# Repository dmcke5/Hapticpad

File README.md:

# CNCDan - Haptic Pad

A 6 button macropad with a display for button labels and a mouse knob with haptic feedback!

[Project Video Link](https://youtu.be/bNUKRJQjuvQ)

#### Features

- 6 Programmable  Macro Buttons
- 128x64 OLED display for button labels and Icons
- Support for up to 256 profiles for a total of 1536 Macros!
- Easy XML configuration, no special drivers required!
- Macro button combinations can be configured with up to 3 simultaneous buttons or 3 seperate button presses with configurable delays between them.
- Micro SD Storage for button labels and config files.
- Haptic feedback mouse wheel with three different modes. Clicky, Twist and Momentum
- RGB ring with configurable colours and 5 different display modes. Halo, Bands, Breath, Rainbow, Solid and Off.
- Easy profile switching with up down profile buttons or profile list display.
- The Last profile is stored to the SD card so the macro pad will start on whichever profile was last active.

#### Bill of Materials

1x 128x64 OLED Display - https://www.waveshare.com/2.42inch-oled-module.htm

1x Magnetic Encoder Board - https://www.aliexpress.com/item/1005007469177411.html

1x 2804 100kv Brushless Gimbal Motor - https://www.aliexpress.com/item/1005006008489660.html

6x Kailh Low Profile Switches - https://www.aliexpress.com/item/1005005066585322.html

1x RP2040-Plus Board - https://www.waveshare.com/rp2040-plus.htm

1x TMC6300 Motor Driver Board - https://www.sparkfun.com/sparkfun-brushless-motor-driver-3-phase-tmc6300.html

1x Micro SD Module - https://www.aliexpress.com/item/1005010587984346.html

4x 6x1mm Magnets - https://www.aliexpress.com/item/1005009894772141.html

2x Tactile Buttons - https://www.digikey.com/en/products/detail/panasonic-electronic-components/EVQ-Q2B03W/762882 (These are the ones I used, but shipping is expensive)

2x Alternative Tactile Buttons - https://www.aliexpress.com/item/1005008326208629.html (These seem like a suitable replacement for the EVQ-Q2B03W switches but I haven't tried them)

The following parts are optional if you want to include the LEDS:

20x WS2811 LED's - https://www.aliexpress.com/item/32776731877.html

20x 0.1uF (100nF) 0603 Capacitors - https://www.aliexpress.com/item/32966526545.html

#### Hardware

9x M3x5x5 Threaded Inserts (only needed for printed housing)

3x M3x6 SHCS

2x M3x10 SHCS

10x M2.5x4 SHCS

4x M3x6 CSK

### Printing Instructions

#### - Printed version
Print all files in the 3D Files/STL's folder. You will need 6 of the keycap file, two of the Menu button file and two of the PCB spacer file.

#### - Machined Version
Print all files in the 3D Files/STL's folder except: "Custom Keycap.STL", "Macro Pad - Printed Version.STL" and "Menu Button Printed.STL"
Get all of the .STEP files in the 3D Files/STEP folder machined. Don't include the Macropad Assembly .STEP file from the main directory as it is a complete model of Macro Pad rather than an individual part. If you supply the MacroPad Housing.PDF file with the housing, you can have the mounting holes tapped for you.

### Motor Assembly

I made this quick picture to show how the wheel motor gets assembled:

The "Encoder Mount.STL" part has two small holes in it that are supposed to get tapped to M2 for the encoder. If you don't have an M2 tap, you can probably just glue the encoder to the mount or even use some small self tapping screws to hold it in place.

The magnet holder should be a snug fit inside the hollow motor shaft. If it isn't, I'd recomend a drop of super glue to ensure it can't work free over time.

### PCB's

You will need to have both PCB's made to complete this project. They are very simple PCB's with only two layers, so they should be cheap!
Just upload the Zip files found in "PCB's/MacroPad" and "PCB's/MacroPad Controller Board" to your PCB manufacturer of choice and they shouldn't need any further info.

#### - Controller Board

The controller board has the main components labelled so you should easily be able to tell where everything goes. I've also labelled power and ground connections on the motor controller and SD reader so just double check you are installing them up the correct way! The SD reader should be flat against the PCB as shown in the video, whilst the motor controller gets installed on its pin headers with the "bottom" of the board face up (the side with the pin labels should be showing). The Pico should also be soldered directly to the board with its USB port facing outwards.
C1 on the Controller board is supposed to be a 10000pF 50v Capacitor. I never ended up fitting mine and I've had no issues but Sparkfun recommended it so I've left the pads there in case you decide to fit it.

#### - Main Board

If you're planning to include the LED's, do them first! There should be one corner of the LED with an arrow shaped rebate. It should point away from the pad labelled with a "1". All of the C components on this board are 0.1uF 0603 size capacitors. They are also needed to make the LED's work.

The switches you need for two profile switching buttons are: EVQ-Q2B03W

They share the same footprint as the EVQ-Q2B02W's but are a bit taller so be careful to ensure you get the right ones!

#### - Connecting the boards

All of the pads on both of the PCB's are actually tiny little through holes, I find these are much more robust for beginners which is why I chose them. The hole is too small to put the wire through so just treat them as a surface mount pad!

The controller board has a set of pads labelled "Display". Use the cable that was included with your screen and solder the wires for the display directly to these pads.
I've matched the labels on my PCB to the display so it should be easy to work out where everything goes.

The two boards get connected together with wires. Just match the labels on both boards and everything should be in the correct spot! I know this is messy compared to a ribbon cable, but I was trying to keep the project as beginner friendly as possible!

The three motor wires get connected to the pins labelled U V and W on the controller board. The software should detect the motor direction when it first starts up so any order for these wires is fine but if you have problems, try swapping two of them!

The Encoder connections are labelled too so just connect the four pins I've included on the board and ignore the remainder of the pins that are on the encoder, we don't need them!

### Software

> [!WARNING] 
> The software is still a work in progress. Everything seen in the video is functional currently, but I'm sure I will have missed some bugs as I've only had time to do some limited testing so far. I will work on clearing as many bugs as I can in the coming weeks but let me know if you run into any! If you're going to submit an issue with a bug, please try and recount your steps to re-create the bug as it will make fixing it much easier!

If you don't wish to compile the code yourself, just copy the latest version of the MacroPad.UF2 file from the software folder and install it directly onto the memory of your Pico using the boot method shown in the video.

You will also need to have your SD card set up correctly in order to use the macro pad.
Copy the entire contents of the "Example SD Card" folder onto you SD card to begin with to ensure everything is working before you start working on your own files.

### XML Config

In the `<Settings>` tag of the XML file you will find all of the settings for the LED's, along with the P and I tuning values for the various wheel modes.

There are 6 acceptable inpts for the `<LED_Mode>` tag. If you spell the words incorrectly the commands won't work, so it would be a good idea to copy and paste from here:

Breath, Bands, Halo, Rainbow, Solid, Off

`<LED_Primary>` and `<LED_Secondary>` are the two colours used in the effects and they are formatted in the order of Red, Green and Blue with values between 0-255. Rainbow and Off obviously don't make use of these colour options and solid just sets the colour to `<LED_Primary>` and ignores `<LED_Secondary>`.

The motor tuning for the printed version of the wheel should be pretty good, so try with my default P and I values first before you do any tuning. I've left out D from the tuning options as it doesn't seem to be needed for this type of feedback and just makes tuning more complex.

In the `<Profiles>` tag is where each profile is stored.

Each profile starts off with a name value assigned like this: `<Profile name="Solidworks">`
Then, there is a `<WheelMode>` and `<WheelKey>` tag. `<WheelKey>` can be any key value from this website https://keycode-visualizer.netlify.app/ and will be held down when the wheel is moving. `<WheelMode>` can only be one of three things: Clicky, Twist or Momentum. Again, these have to be exact so copy and paste from here to ensure they work.

Next is a `<MacroButtons>` tag that holds all of our Macro buttons for the profile.

Each macro button looks like this: 
```
<MacroButton>
    <Action>0,68</Action>
    <Action>0,0</Action>
    <Action>0,0</Action>
    <Label>Dimension</Label>
</MacroButton>
```
There will be 6 of these sections per profile. Each action has two values, the first is the delay (in milliseconds) to perform before the action, followed by the keycode you wish to press (using the same website I linked earlier). Setting both of these values to 0 for any of the three actions will mean nothing happens for that action.
Label is simply the name that will appear on screen for that button.

And that's it! just replicate that first example profile as many times as you like (up to 256 times, anyway) and each one will create a new profile that you can store your macros in.

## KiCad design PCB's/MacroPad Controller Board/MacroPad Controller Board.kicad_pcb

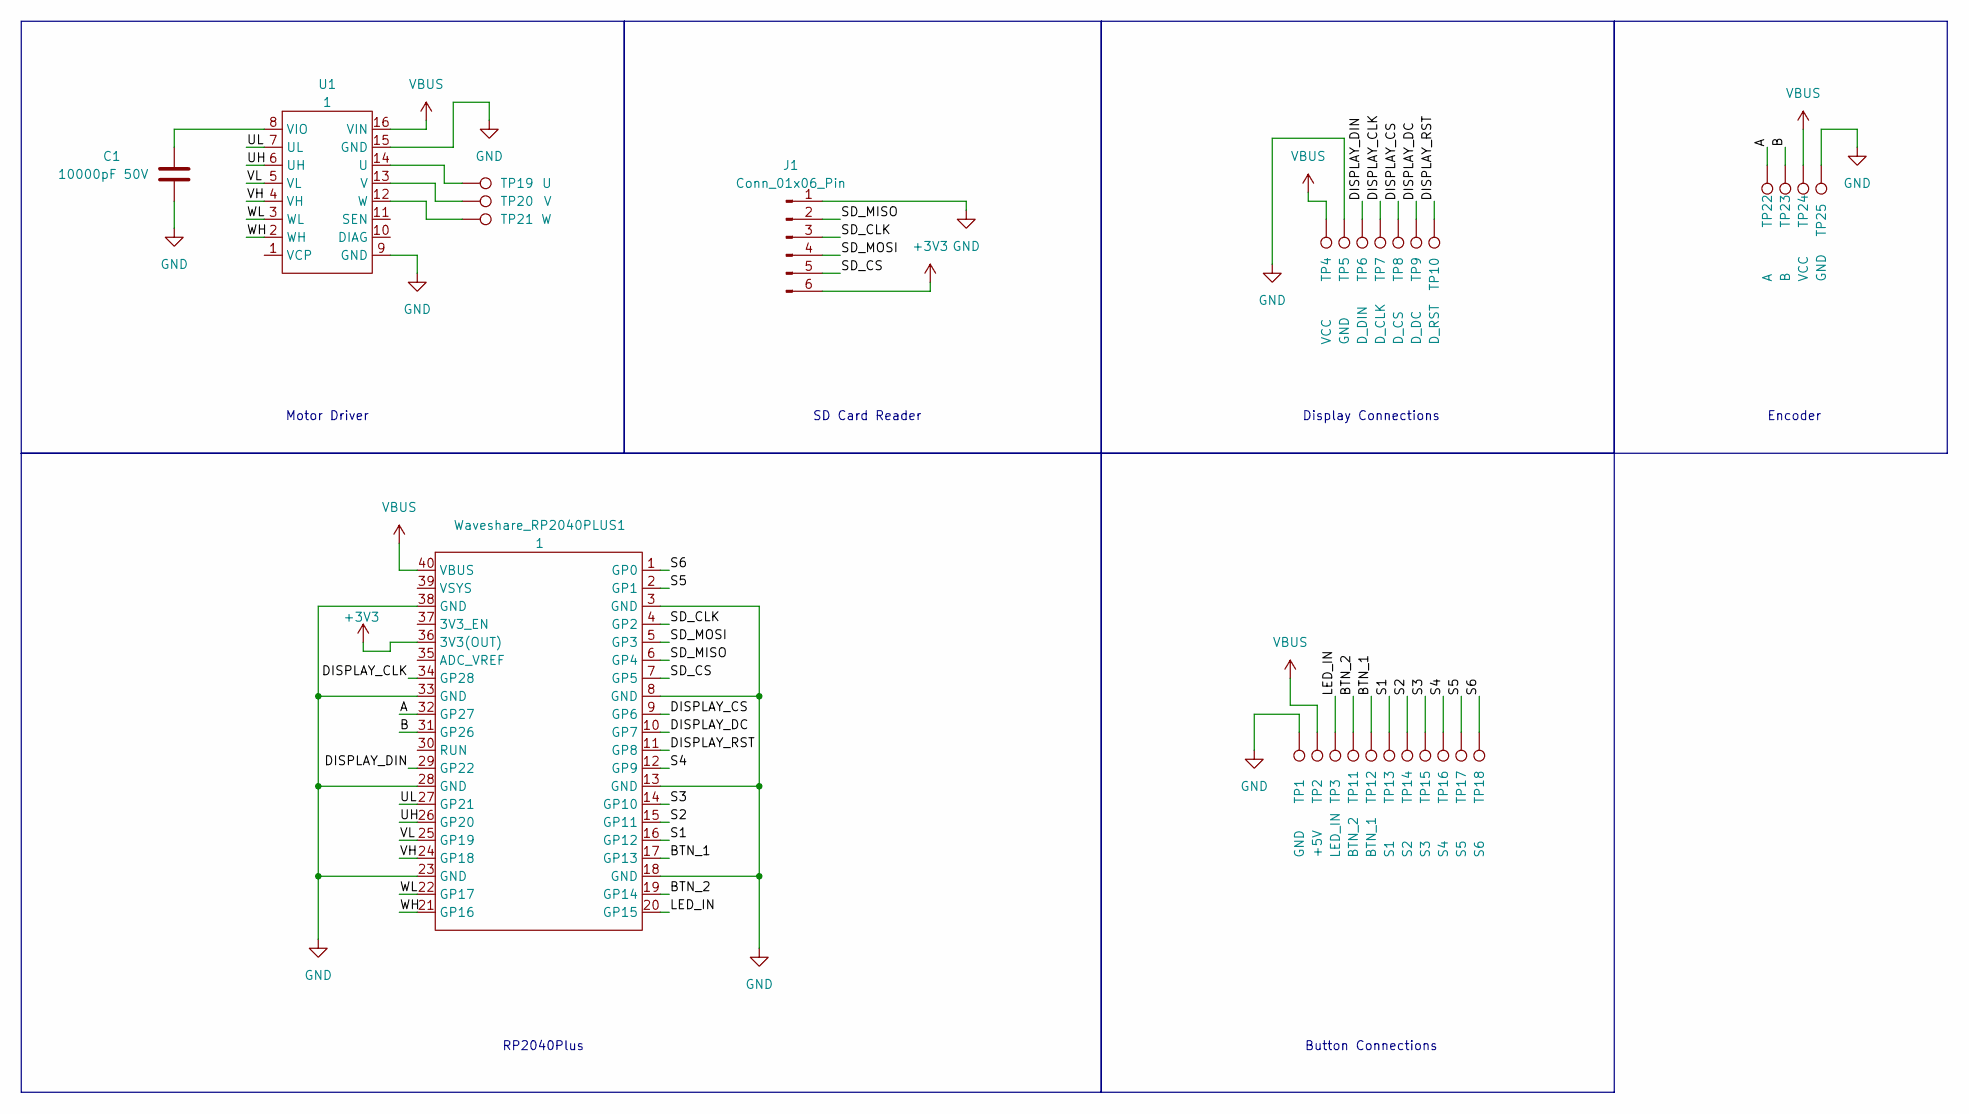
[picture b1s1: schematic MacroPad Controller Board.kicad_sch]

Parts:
C1: 10000pF 50V; C_0603_1608Metric_Pad1.08x0.95mm_HandSolder
J1: Conn_01x06_Pin; PinHeader_1x06_P2.54mm_Vertical
TP1, TP5, TP25: GND; TestPoint_THTPad_D1.0mm_Drill0.5mm
TP2: +5V; TestPoint_THTPad_D1.0mm_Drill0.5mm
TP3: LED_IN; TestPoint_THTPad_D1.0mm_Drill0.5mm
TP4, TP24: VCC; TestPoint_THTPad_D1.0mm_Drill0.5mm
TP6: D_DIN; TestPoint_THTPad_D1.0mm_Drill0.5mm
TP7: D_CLK; TestPoint_THTPad_D1.0mm_Drill0.5mm
TP8: D_CS; TestPoint_THTPad_D1.0mm_Drill0.5mm
TP9: D_DC; TestPoint_THTPad_D1.0mm_Drill0.5mm
TP10: D_RST; TestPoint_THTPad_D1.0mm_Drill0.5mm
TP11: BTN_2; TestPoint_THTPad_D1.0mm_Drill0.5mm
TP12: BTN_1; TestPoint_THTPad_D1.0mm_Drill0.5mm
TP13: S1; TestPoint_THTPad_D1.0mm_Drill0.5mm
TP14: S2; TestPoint_THTPad_D1.0mm_Drill0.5mm
TP15: S3; TestPoint_THTPad_D1.0mm_Drill0.5mm
TP16: S4; TestPoint_THTPad_D1.0mm_Drill0.5mm
TP17: S5; TestPoint_THTPad_D1.0mm_Drill0.5mm
TP18: S6; TestPoint_THTPad_D1.0mm_Drill0.5mm
TP19: U; TestPoint_THTPad_D2.0mm_Drill1.0mm
TP20: V; TestPoint_THTPad_D2.0mm_Drill1.0mm
TP21: W; TestPoint_THTPad_D2.0mm_Drill1.0mm
TP22: A; TestPoint_THTPad_D1.0mm_Drill0.5mm
TP23: B; TestPoint_THTPad_D1.0mm_Drill0.5mm
U1: 1; Sparkfun_TMC6300
Waveshare_RP2040PLUS1: 1; RP2040PLUS_SMD

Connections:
+3V3: J1.6, Waveshare_RP2040PLUS1.36 (3V3(OUT)); also elsewhere on the board
/A: TP22.1, Waveshare_RP2040PLUS1.32 (GP27); also elsewhere on the board
/B: TP23.1, Waveshare_RP2040PLUS1.31 (GP26); also elsewhere on the board
/BTN_1: TP12.1, Waveshare_RP2040PLUS1.17 (GP13); also elsewhere on the board
/BTN_2: TP11.1, Waveshare_RP2040PLUS1.19 (GP14); also elsewhere on the board
/DISPLAY_CLK: TP7.1, Waveshare_RP2040PLUS1.34 (GP28); also elsewhere on the board
/DISPLAY_CS: TP8.1, Waveshare_RP2040PLUS1.9 (GP6); also elsewhere on the board
/DISPLAY_DC: TP9.1, Waveshare_RP2040PLUS1.10 (GP7); also elsewhere on the board
/DISPLAY_DIN: TP6.1, Waveshare_RP2040PLUS1.29 (GP22); also elsewhere on the board
/DISPLAY_RST: TP10.1, Waveshare_RP2040PLUS1.11 (GP8); also elsewhere on the board
/LED_IN: TP3.1, Waveshare_RP2040PLUS1.20 (GP15); also elsewhere on the board
/S1: TP13.1, Waveshare_RP2040PLUS1.16 (GP12); also elsewhere on the board
/S2: TP14.1, Waveshare_RP2040PLUS1.15 (GP11); also elsewhere on the board
/S3: TP15.1, Waveshare_RP2040PLUS1.14 (GP10); also elsewhere on the board
/S4: TP16.1, Waveshare_RP2040PLUS1.12 (GP9); also elsewhere on the board
/S5: TP17.1, Waveshare_RP2040PLUS1.2 (GP1); also elsewhere on the board
/S6: TP18.1, Waveshare_RP2040PLUS1.1 (GP0); also elsewhere on the board
/SD_CLK: J1.3, Waveshare_RP2040PLUS1.4 (GP2); also elsewhere on the board
/SD_CS: J1.5, Waveshare_RP2040PLUS1.7 (GP5); also elsewhere on the board
/SD_MISO: J1.2, Waveshare_RP2040PLUS1.6 (GP4); also elsewhere on the board
/SD_MOSI: J1.4, Waveshare_RP2040PLUS1.5 (GP3); also elsewhere on the board
/UH: U1.6 (UH), Waveshare_RP2040PLUS1.26 (GP20); also elsewhere on the board
/UL: U1.7 (UL), Waveshare_RP2040PLUS1.27 (GP21); also elsewhere on the board
/VH: U1.4 (VH), Waveshare_RP2040PLUS1.24 (GP18); also elsewhere on the board
/VL: U1.5 (VL), Waveshare_RP2040PLUS1.25 (GP19); also elsewhere on the board
/WH: U1.2 (WH), Waveshare_RP2040PLUS1.21 (GP16); also elsewhere on the board
/WL: U1.3 (WL), Waveshare_RP2040PLUS1.22 (GP17); also elsewhere on the board
GND: C1.2, J1.1, TP1.1, TP5.1, TP25.1, U1.9 (GND), U1.15 (GND), Waveshare_RP2040PLUS1.3 (GND), Waveshare_RP2040PLUS1.8 (GND), Waveshare_RP2040PLUS1.13 (GND), Waveshare_RP2040PLUS1.18 (GND), Waveshare_RP2040PLUS1.23 (GND), Waveshare_RP2040PLUS1.28 (GND), Waveshare_RP2040PLUS1.33 (GND), Waveshare_RP2040PLUS1.38 (GND); also elsewhere on the board
unnamed: TP19.1, U1.14 (U)
unnamed: TP20.1, U1.13 (V)
unnamed: C1.1, U1.8 (VIO)
unnamed: TP21.1, U1.12 (W)
VBUS: TP2.1, TP4.1, TP24.1, U1.16 (VIN), Waveshare_RP2040PLUS1.40 (VBUS); also elsewhere on the board

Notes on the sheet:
Motor Driver
SD Card Reader
RP2040Plus
Display Connections
Button Connections
Encoder

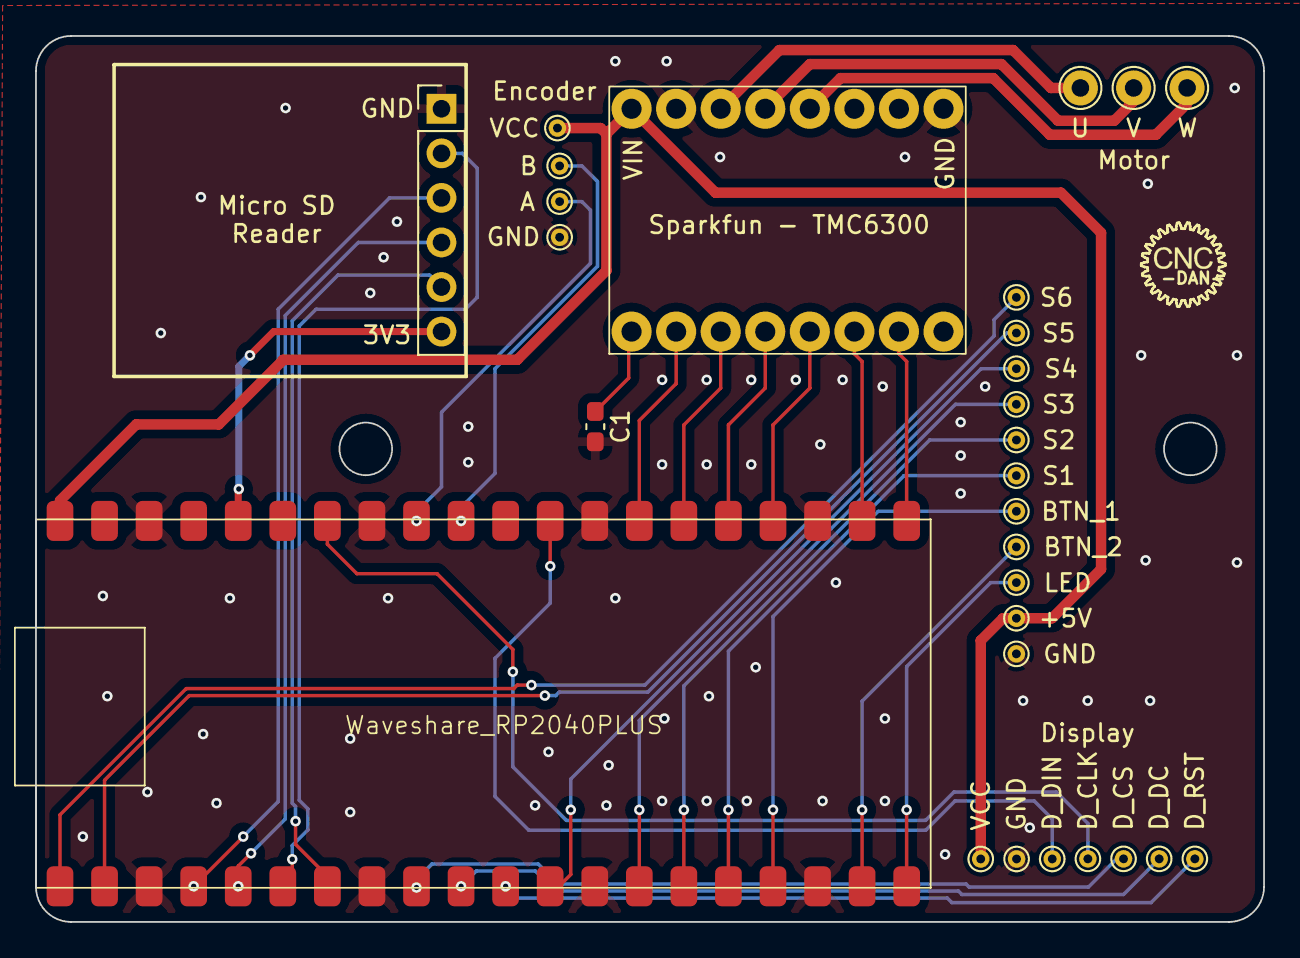
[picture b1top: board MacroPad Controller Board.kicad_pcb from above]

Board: 2 copper layers, 70.0 x 50.5 mm, 29 parts (0 on the bottom side), 33 nets.

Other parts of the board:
Waveshare_RP2040PLUS: 1; RP2040PLUS_SMD

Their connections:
+3V3: Waveshare_RP2040PLUS.36 (3V3(OUT)); also elsewhere on the board
/A: Waveshare_RP2040PLUS.32 (GP27); also elsewhere on the board
/B: Waveshare_RP2040PLUS.31 (GP26); also elsewhere on the board
/BTN_1: Waveshare_RP2040PLUS.17 (GP13); also elsewhere on the board
/BTN_2: Waveshare_RP2040PLUS.19 (GP14); also elsewhere on the board
/DISPLAY_CLK: Waveshare_RP2040PLUS.34 (GP28); also elsewhere on the board
/DISPLAY_CS: Waveshare_RP2040PLUS.9 (GP6); also elsewhere on the board
/DISPLAY_DC: Waveshare_RP2040PLUS.10 (GP7); also elsewhere on the board
/DISPLAY_DIN: Waveshare_RP2040PLUS.29 (GP22); also elsewhere on the board
/DISPLAY_RST: Waveshare_RP2040PLUS.11 (GP8); also elsewhere on the board
/LED_IN: Waveshare_RP2040PLUS.20 (GP15); also elsewhere on the board
/S1: Waveshare_RP2040PLUS.16 (GP12); also elsewhere on the board
/S2: Waveshare_RP2040PLUS.15 (GP11); also elsewhere on the board
/S3: Waveshare_RP2040PLUS.14 (GP10); also elsewhere on the board
/S4: Waveshare_RP2040PLUS.12 (GP9); also elsewhere on the board
/S5: Waveshare_RP2040PLUS.2 (GP1); also elsewhere on the board
/S6: Waveshare_RP2040PLUS.1 (GP0); also elsewhere on the board
/SD_CLK: Waveshare_RP2040PLUS.4 (GP2); also elsewhere on the board
/SD_CS: Waveshare_RP2040PLUS.7 (GP5); also elsewhere on the board
/SD_MISO: Waveshare_RP2040PLUS.6 (GP4); also elsewhere on the board
/SD_MOSI: Waveshare_RP2040PLUS.5 (GP3); also elsewhere on the board
/UH: Waveshare_RP2040PLUS.26 (GP20); also elsewhere on the board
/UL: Waveshare_RP2040PLUS.27 (GP21); also elsewhere on the board
/VH: Waveshare_RP2040PLUS.24 (GP18); also elsewhere on the board
/VL: Waveshare_RP2040PLUS.25 (GP19); also elsewhere on the board
/WH: Waveshare_RP2040PLUS.21 (GP16); also elsewhere on the board
/WL: Waveshare_RP2040PLUS.22 (GP17); also elsewhere on the board
GND: Waveshare_RP2040PLUS.3 (GND), Waveshare_RP2040PLUS.8 (GND), Waveshare_RP2040PLUS.13 (GND), Waveshare_RP2040PLUS.18 (GND), Waveshare_RP2040PLUS.23 (GND), Waveshare_RP2040PLUS.28 (GND), Waveshare_RP2040PLUS.33 (GND), Waveshare_RP2040PLUS.38 (GND); also elsewhere on the board
VBUS: Waveshare_RP2040PLUS.40 (VBUS); also elsewhere on the board

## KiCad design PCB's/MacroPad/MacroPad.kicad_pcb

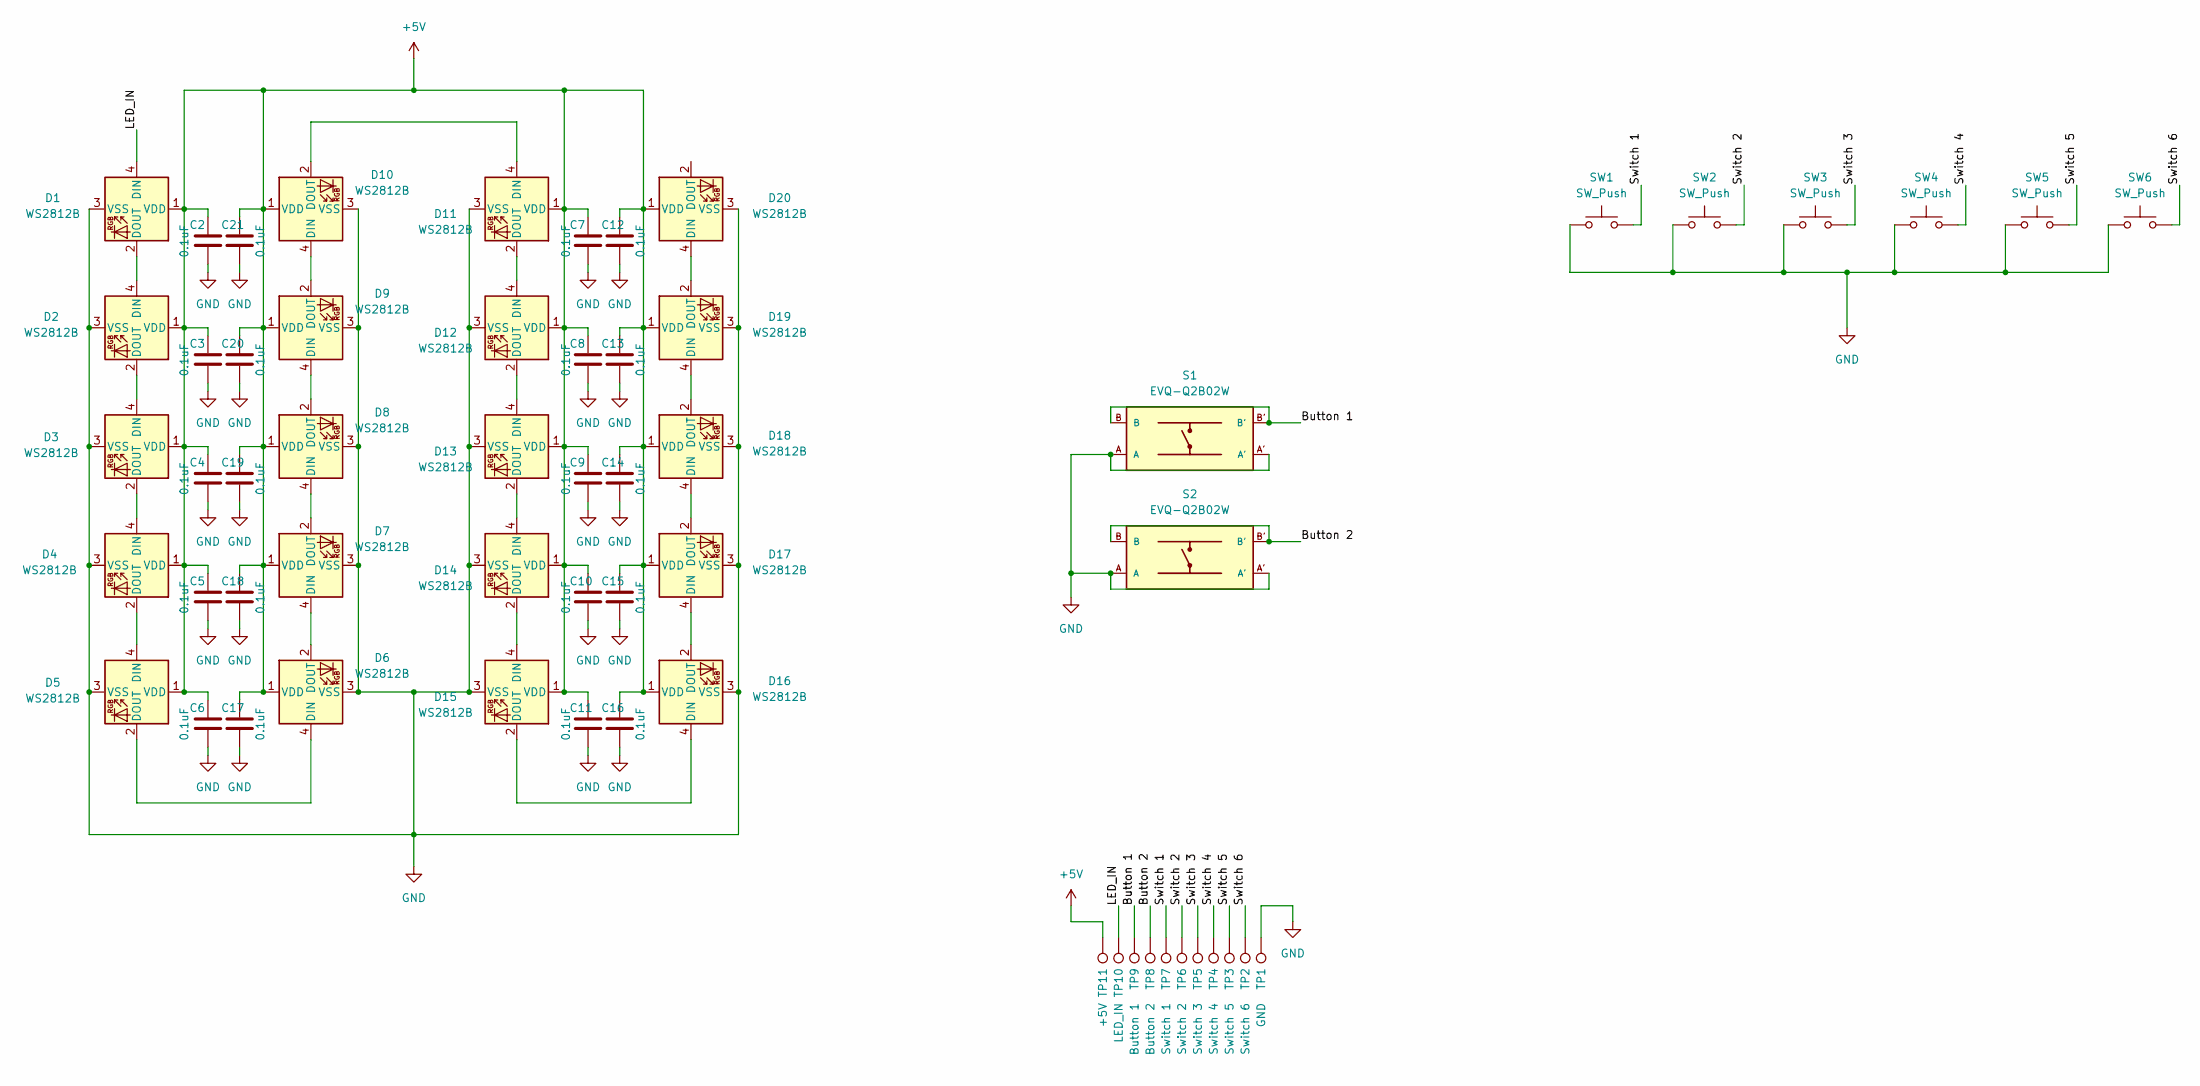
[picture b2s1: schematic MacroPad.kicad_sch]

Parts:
C2, C3, C4, C5, C6, C7, C8, C9, C10, C11, C12, C13, C14, C15, C16, C17, C18, C19, C20, C21: 0.1uF; C_0603_1608Metric
D1, D2, D3, D4, D5, D6, D7, D8, D9, D10, D11, D12, D13, D14, D15, D16, D17, D18, D19, D20: WS2812B; LED_WS2812B_PLCC4_5.0x5.0mm_P3.2mm
S1, S2: EVQ-Q2B02W; SW_EVQ-Q2B02W
SW1, SW2, SW3, SW4, SW5, SW6: SW_Push; SW_PG1350_reversible
TP1: GND; TestPoint_THTPad_D1.0mm_Drill0.5mm
TP2: Switch 6; TestPoint_THTPad_D1.0mm_Drill0.5mm
TP3: Switch 5; TestPoint_THTPad_D1.0mm_Drill0.5mm
TP4: Switch 4; TestPoint_THTPad_D1.0mm_Drill0.5mm
TP5: Switch 3; TestPoint_THTPad_D1.0mm_Drill0.5mm
TP6: Switch 2; TestPoint_THTPad_D1.0mm_Drill0.5mm
TP7: Switch 1; TestPoint_THTPad_D1.0mm_Drill0.5mm
TP8: Button 2; TestPoint_THTPad_D1.0mm_Drill0.5mm
TP9: Button 1; TestPoint_THTPad_D1.0mm_Drill0.5mm
TP10: LED_IN; TestPoint_THTPad_D1.0mm_Drill0.5mm
TP11: +5V; TestPoint_THTPad_D1.0mm_Drill0.5mm

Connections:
+5V: C2.1, C3.1, C4.1, C5.1, C6.1, C7.1, C8.1, C9.1, C10.1, C11.1, C12.1, C13.1, C14.1, C15.1, C16.1, C17.1, C18.1, C19.1, C20.1, C21.1, D1.1 (VDD), D2.1 (VDD), D3.1 (VDD), D4.1 (VDD), D5.1 (VDD), D6.1 (VDD), D7.1 (VDD), D8.1 (VDD), D9.1 (VDD), D10.1 (VDD), D11.1 (VDD), D12.1 (VDD), D13.1 (VDD), D14.1 (VDD), D15.1 (VDD), D16.1 (VDD), D17.1 (VDD), D18.1 (VDD), D19.1 (VDD), D20.1 (VDD), TP11.1
/Button 1: S1.B, S1.B', TP9.1
/Button 2: S2.B, S2.B', TP8.1
/LED_IN: D1.4 (DIN), TP10.1
/Switch 1: SW1.2, TP7.1
/Switch 2: SW2.2, TP6.1
/Switch 3: SW3.2, TP5.1
/Switch 4: SW4.2, TP4.1
/Switch 5: SW5.2, TP3.1
/Switch 6: SW6.2, TP2.1
GND: C2.2, C3.2, C4.2, C5.2, C6.2, C7.2, C8.2, C9.2, C10.2, C11.2, C12.2, C13.2, C14.2, C15.2, C16.2, C17.2, C18.2, C19.2, C20.2, C21.2, D1.3 (VSS), D2.3 (VSS), D3.3 (VSS), D4.3 (VSS), D5.3 (VSS), D6.3 (VSS), D7.3 (VSS), D8.3 (VSS), D9.3 (VSS), D10.3 (VSS), D11.3 (VSS), D12.3 (VSS), D13.3 (VSS), D14.3 (VSS), D15.3 (VSS), D16.3 (VSS), D17.3 (VSS), D18.3 (VSS), D19.3 (VSS), D20.3 (VSS), S1.A, S1.A', S2.A, S2.A', SW1.1, SW2.1, SW3.1, SW4.1, SW5.1, SW6.1, TP1.1
unnamed: D1.2 (DOUT), D2.4 (DIN)
unnamed: D2.2 (DOUT), D3.4 (DIN)
unnamed: D3.2 (DOUT), D4.4 (DIN)
unnamed: D4.2 (DOUT), D5.4 (DIN)
unnamed: D5.2 (DOUT), D6.4 (DIN)
unnamed: D6.2 (DOUT), D7.4 (DIN)
unnamed: D7.2 (DOUT), D8.4 (DIN)
unnamed: D8.2 (DOUT), D9.4 (DIN)
unnamed: D9.2 (DOUT), D10.4 (DIN)
unnamed: D10.2 (DOUT), D11.4 (DIN)
unnamed: D11.2 (DOUT), D12.4 (DIN)
unnamed: D12.2 (DOUT), D13.4 (DIN)
unnamed: D13.2 (DOUT), D14.4 (DIN)
unnamed: D14.2 (DOUT), D15.4 (DIN)
unnamed: D15.2 (DOUT), D16.4 (DIN)
unnamed: D16.2 (DOUT), D17.4 (DIN)
unnamed: D17.2 (DOUT), D18.4 (DIN)
unnamed: D18.2 (DOUT), D19.4 (DIN)
unnamed: D19.2 (DOUT), D20.4 (DIN)

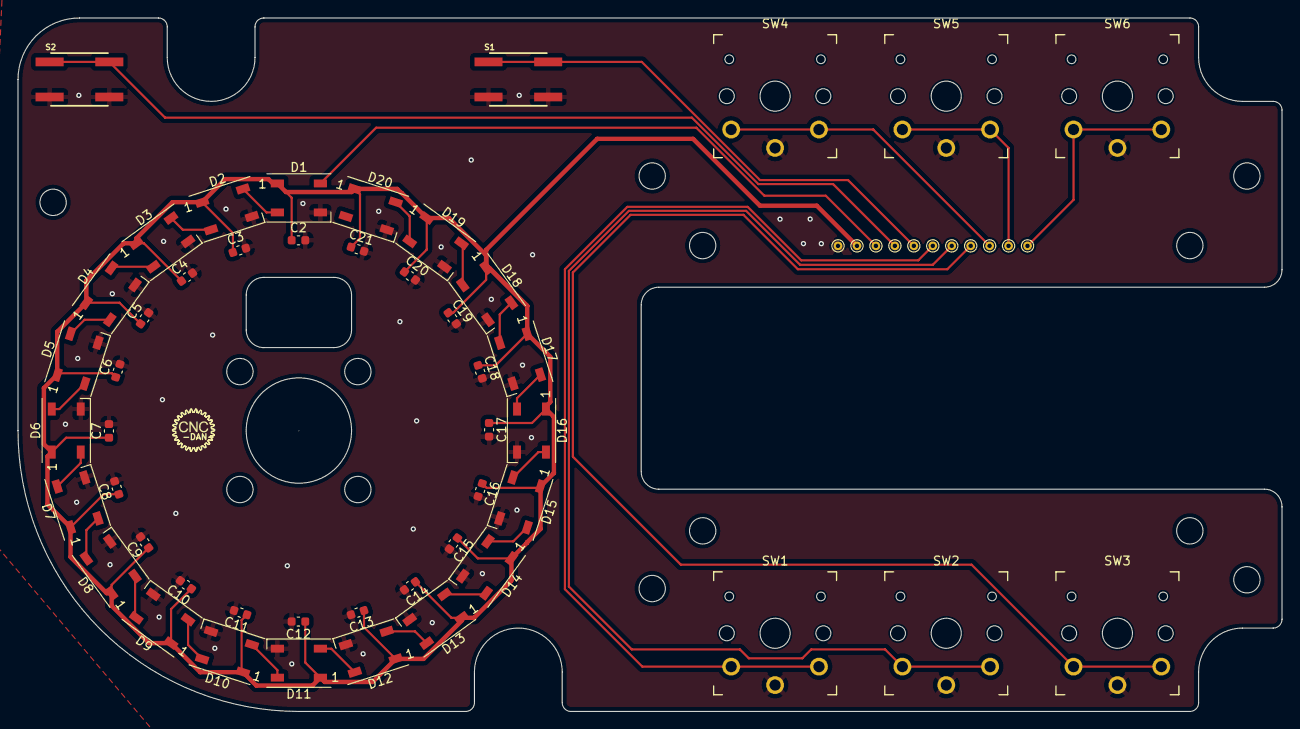
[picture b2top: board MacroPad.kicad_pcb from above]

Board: 2 copper layers, 144.0 x 79.0 mm, 59 parts (0 on the bottom side), 30 nets.

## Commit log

2026-01-09 Added license and readme
2026-01-09 Updated Motor Assembly Drawing
2026-01-10 Added PCB's
2026-01-13 Update tactile button information in README
    Added alternative tactile button options and shipping note.
2026-01-13 Fix typo in README for alternative tactile buttons
2026-03-28 Added macro configurator tool
